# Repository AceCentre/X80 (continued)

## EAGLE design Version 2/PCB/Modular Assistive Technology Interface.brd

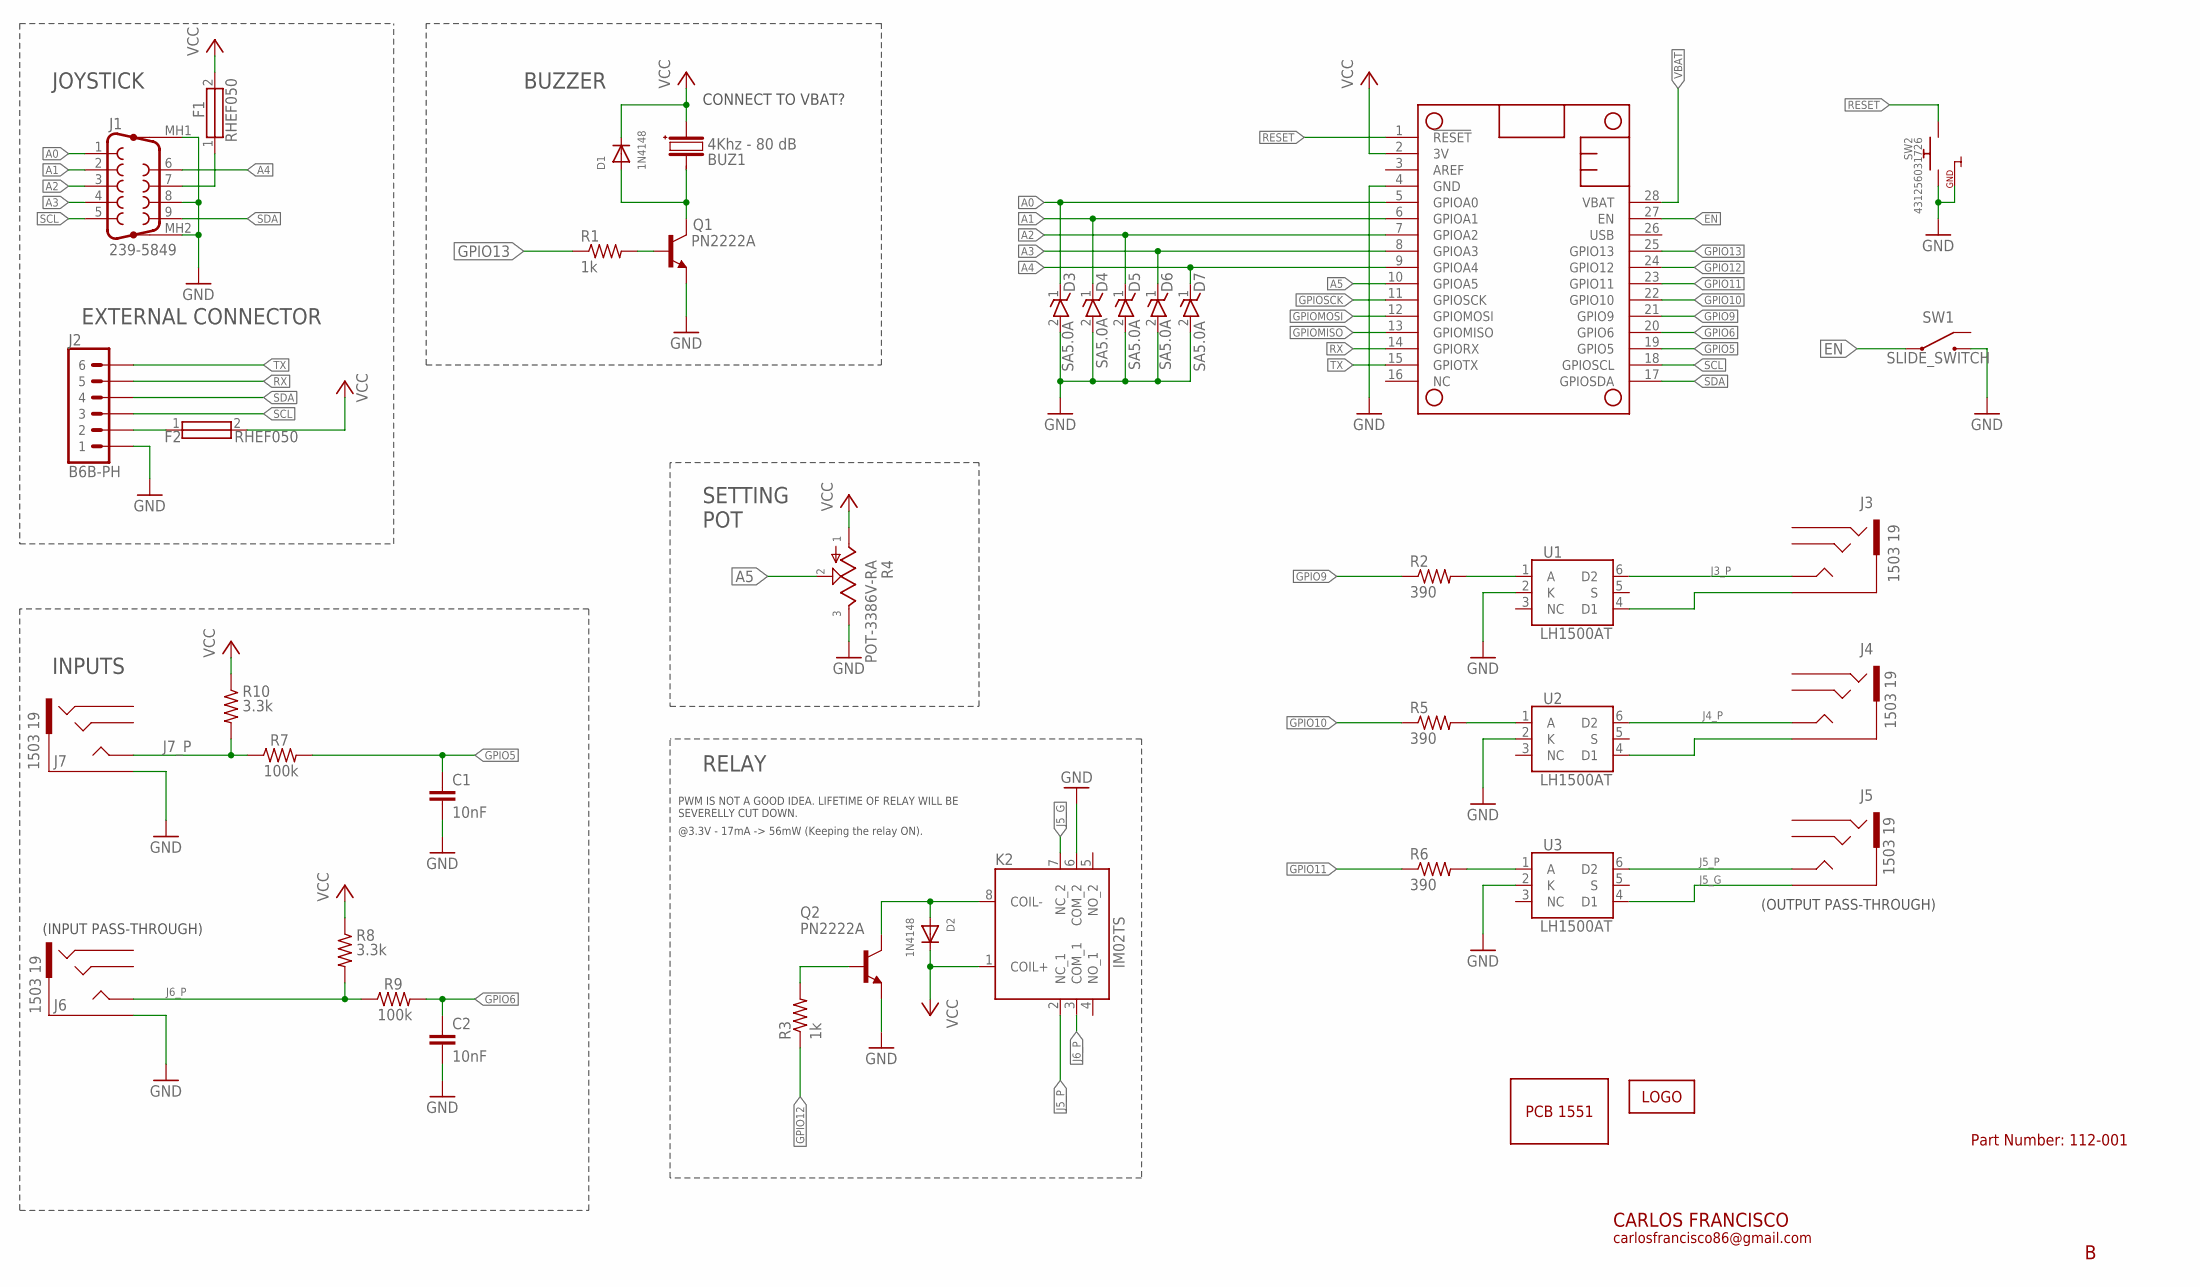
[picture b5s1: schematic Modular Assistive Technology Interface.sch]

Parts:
BUZ1: 4Khz - 80 dB; -511-7620
C1, C2: 10nF; C025-024X044
D1, D2: 1N4148; DO-1N4148
D3, D4, D5, D6, D7: SA5.0A; DIOAD1910W86L670D310
F1, F2: RHEF050
J1: 239-5849; DB9_PLUG_SLOT
J2: B6B-PH; SHDR6W50P0X200_1X6_990X450X600
J3, J4, J5, J6, J7: 1503 19; 1503-19
K2: IM02TS; IM03TS114620378
MS1: FEATHERWING_NODIM; FEATHERWING_DIM
Q1, Q2: PN2222A; TO92-EBC-OVAL
R1, R3: 1k; 0207/10
R2, R5, R6: 390; 0207/10
R4: POT-3386V-RA; 3386V1103LF
R7, R9: 100k; 0207/10
R8, R10: 3.3k; 0207/10
SW1: SLIDE_SWITCH; OS102011MA1QN1
SW2: 431256031726; SERIES95C_RA
U1, U2, U3: LH1500AT; DIP762W47P254L880H410Q6N
U$2: LOGO-10MM; LOGO_10MM
U$3: PCB_1551-1551; PCB

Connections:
A0: D3.1 (K), J1.1, MS1.5 (GPIOA0)
A1: D4.1 (K), J1.2, MS1.6 (GPIOA1)
A2: D5.1 (K), J1.3, MS1.7 (GPIOA2)
A3: D6.1 (K), J1.4, MS1.8 (GPIOA3)
A4: D7.1 (K), J1.6, MS1.9 (GPIOA4)
A5: MS1.10 (GPIOA5), R4.2
BUZ_CTRL_R: Q1.B, R1.2
EN: MS1.27 (EN), SW1.2
GND: C1.2, C2.2, D3.2 (A), D4.2 (A), D5.2 (A), D6.2 (A), D7.2 (A), J1.8, J1.MH1 (G1), J1.MH2 (G2), J2.1, J6.1, J7.1, K2.6 (COM_2), MS1.4 (GND), Q1.E, Q2.E, R4.3, SW1.1, SW2.F1 (GND), SW2.F2 (GND), SW2.T2 (SW2), U1.2 (K), U2.2 (K), U3.2 (K)
GPIO5: C1.1, MS1.19 (GPIO5), R7.2
GPIO6: C2.1, MS1.20 (GPIO6), R9.2
GPIO9: MS1.21 (GPIO9), R2.1
GPIO10: MS1.22 (GPIO10), R5.1
GPIO11: MS1.23 (GPIO11), R6.1
GPIO12: MS1.24 (GPIO12), R3.1
GPIO13: MS1.25 (GPIO13), R1.1
GPIOMISO: MS1.13 (GPIOMISO)
GPIOMOSI: MS1.12 (GPIOMOSI)
GPIOSCK: MS1.11 (GPIOSCK)
J3_P: J3.4, J3.5 (4), U1.6 (D2)
J4_P: J4.4, J4.5 (4), U2.6 (D2)
J5_G: J5.1, K2.7 (NC_2), U3.4 (D1)
J5_P: J5.4, J5.5 (4), K2.2 (NC_1), U3.6 (D2)
J6_P: J6.4, J6.5 (4), K2.3 (COM_1), R8.2, R9.1
J7_P: J7.4, J7.5 (4), R7.1, R10.2
unnamed: BUZ1.-, D1.A, Q1.C
unnamed: J3.1, U1.4 (D1)
unnamed: J4.1, U2.4 (D1)
unnamed: R2.2, U1.1 (A)
unnamed: R5.2, U2.1 (A)
unnamed: R6.2, U3.1 (A)
unnamed: F2.1, J2.2
unnamed: D2.A, K2.8 (COIL-), Q2.C
unnamed: Q2.B, R3.2
unnamed: F1.1, J1.7
RESET: MS1.1 (!RESET), SW2.T1 (SW1)
RX: J2.5, MS1.14 (GPIORX)
SCL: J1.5, J2.3, MS1.18 (GPIOSCL)
SDA: J1.9, J2.4, MS1.17 (GPIOSDA)
TX: J2.6, MS1.15 (GPIOTX)
VBAT: MS1.28 (VBAT)
VCC: BUZ1.+, D1.C, D2.C, F1.2, F2.2, K2.1 (COIL+), MS1.2 (3V), R4.1, R8.1, R10.1

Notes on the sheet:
CONNECT TO VBAT?
CARLOS FRANCISCO
carlosfrancisco86@gmail.com
BUZZER
JOYSTICK
EXTERNAL CONNECTOR
SETTING POT
(INPUT PASS-THROUGH)
INPUTS
(OUTPUT PASS-THROUGH)
RELAY
PWM IS NOT A GOOD IDEA. LIFETIME OF RELAY WILL BE SEVERELLY CUT DOWN.
Part Number: 112-001
@3.3V - 17mA -> 56mW (Keeping the relay ON).

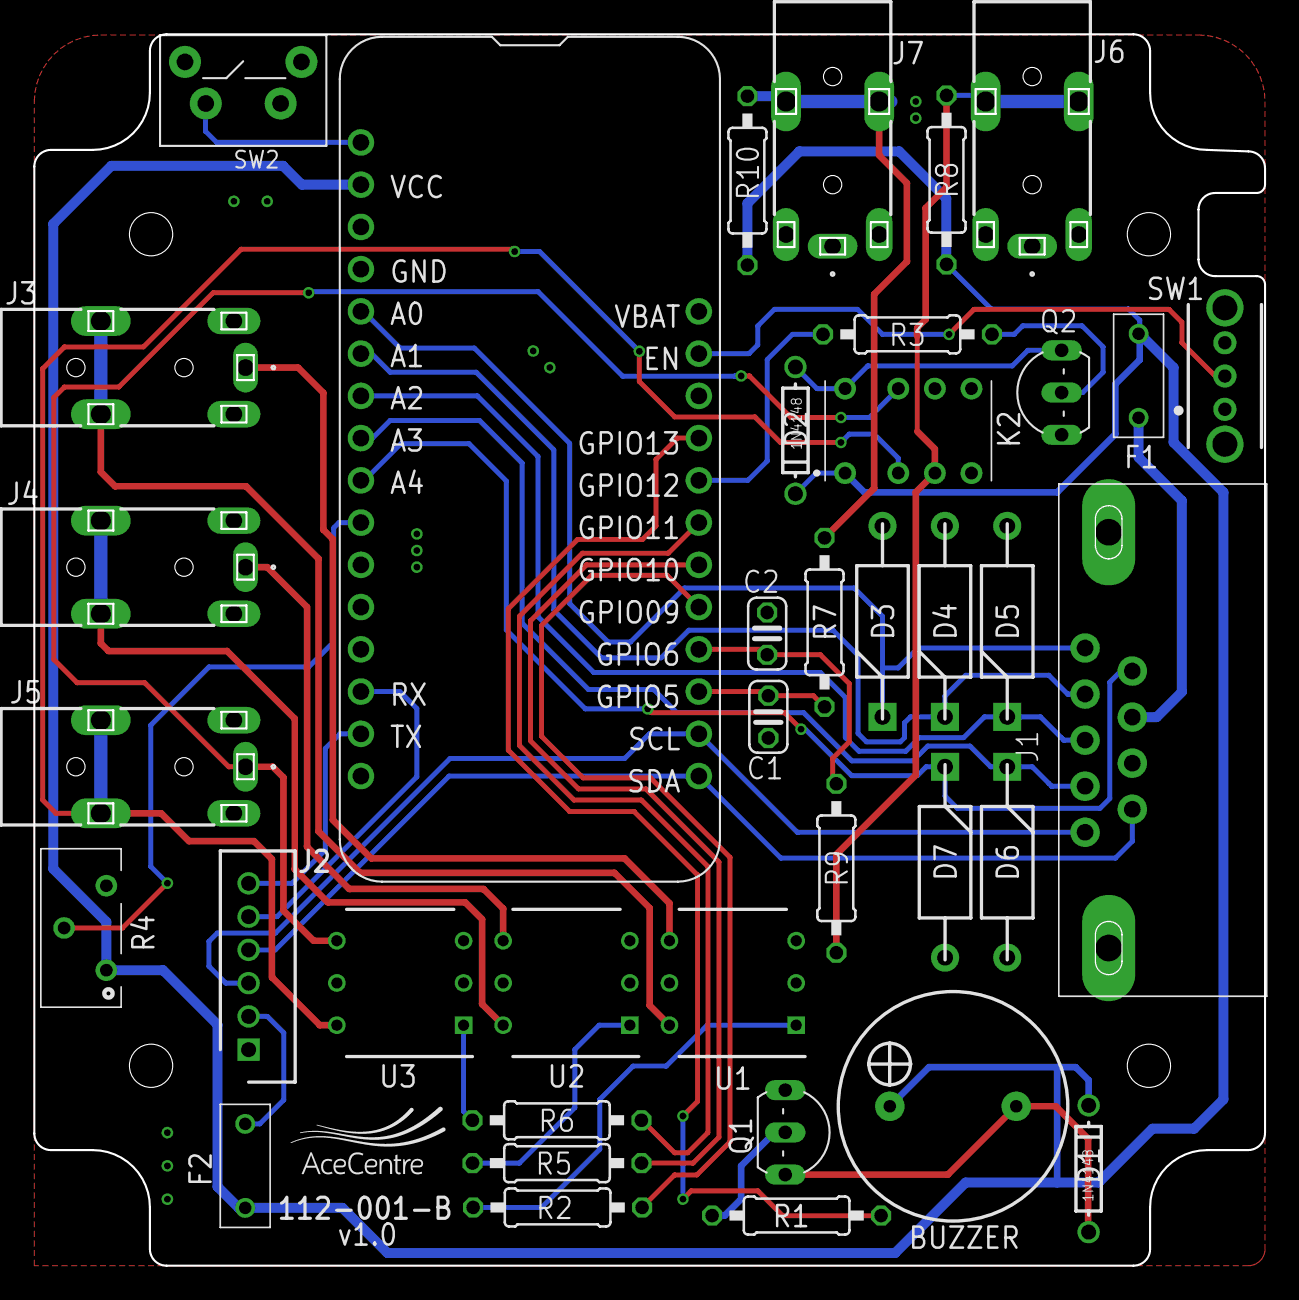
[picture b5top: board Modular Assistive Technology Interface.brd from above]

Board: 2 copper layers, 74.0 x 74.0 mm, 40 parts (0 on the bottom side), 38 nets.

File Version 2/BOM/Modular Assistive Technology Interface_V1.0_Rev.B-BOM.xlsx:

Item # | Ref Des | Qty | Description | Manufacturer | Manufacturer part-name | Value | Package | RS-ONLINE_NUM
1 | BUZ1 | 1 | 80dB, Through Hole Continuous Internal Piezo Buzzer | RS-PRO | 511-7620 | 4Khz, 80dB | THT | 511-7620
2 | C1, C2 | 2 | 10nF Multilayer Ceramic Capacitor MLCC 50V dc ±10% | KEMET | C315C103K5R5TA | 10nF | THT | 538-1196
3 | D1, D2 | 2 | Switching Diode, 400mA 100V, 2-Pin DO-35 1N4148TR | On Semiconductor | 1N4148TR | 1N4148 | THT | 671-5477
4 | D3, D4, D5, D6, D7 | 5 | SA5.0A, Uni-Directional TVS Diode, 500W, 2-Pin DO-204AC | Littelfuse | SA5.0A | 9.2V | THT | 764-5521
5 | F1, F2 | 2 | 0.5A Radial Leaded PCB Mount Resettable Fuse, 30 V | Littelfuse | RHEF050 | 0.5A | THT | 506-971
6 | J1 | 1 | D-sub Connector - 2.77mm Pitch | RS-PRO | 239-5849 | 239-5849 | THT | 239-5849
7 | J2 | 1 | JST, PH, B6B, 6 Way, 1 Row, Straight PCB Header | JST | B6B-PH-K-S(LF)(SN) | B6B-PH | THT | 820-1447
8 | J3, J4, J5, J6, J7 | 5 | 3.5 mm PCB Mount Stereo Jack Socket, 4Pole 1A | Lumberg | 1503 19 | Jack | THT | 124-8885
9 | K2 | 1 | DPDT telecom PCB relay, 2A 5Vdc coil, EA | TE Connectivity | IM02TS | DPDT Relay | THT | 422-7013
10 | Q1, Q2 | 2 | NPN General-Purpose Amplifier | On Semiconductor | PN2222ABU | PN2222A | THT | 739-0555
11 | R1, R3 | 2 | RS PRO 1kΩ Carbon Film Resistor 0.25W ±5% | RS-PRO | 707-7666 | 1k | THT | 707-7666
12 | R2, R5, R6 | 3 | RS PRO 390Ω Carbon Film Resistor 0.25W ±5% | RS-PRO | 707-7634 | 390R | THT | 707-7634
13 | R4 | 1 | 10kΩ, ±10%, 0.5W Linear potentiometer | Bourns | 3386V-1-103LF | 10k | THT | 691-7658
14 | R7, R9 | 2 | RS PRO 100kΩ Carbon Film Resistor 0.25W ±5% | RS-PRO | 707-7824 | 100k | THT | 707-7824
15 | R8, R10 | 2 | RS PRO 3.3kΩ Carbon Film Resistor 0.25W ±5% | RS-PRO | 707-7701 | 3,3k | THT | 707-7701
16 | SW1 | 1 | Through Hole Slide Switch Single Pole Double Throw (SPDT) | C&K Components | OS102011MA1QN1 | SPDT | THT | 787-4855
17 | SW2 | 1 | Tactile Switch, Single Pole Single Throw (SPST) 50 mA @ 12 V | Wurth Elektronik | 431256031726 | 431256031726 | THT | 785-6386
18 | U1, U2, U3 | 3 | 1 Form A Solid-State Relay (NO) | Vishay | LH1500AT | LH1500AT | THT | 180-8794
19 | Socket Headers (Feather) x16 | 1 | SSW 2.54mm Pitch 16 Way 1 Row Straight PCB Socket | Samtec | SSW-116-01-G-S | 16-Way | THT | 765-5792
20 | Socket Headers (Feather) x12 | 1 | SSW 2.54mm Pitch 12 Way 1 Row Straight PCB Socket | Samtec | SSW-112-01-G-S | 12-Way | THT | 765-5751

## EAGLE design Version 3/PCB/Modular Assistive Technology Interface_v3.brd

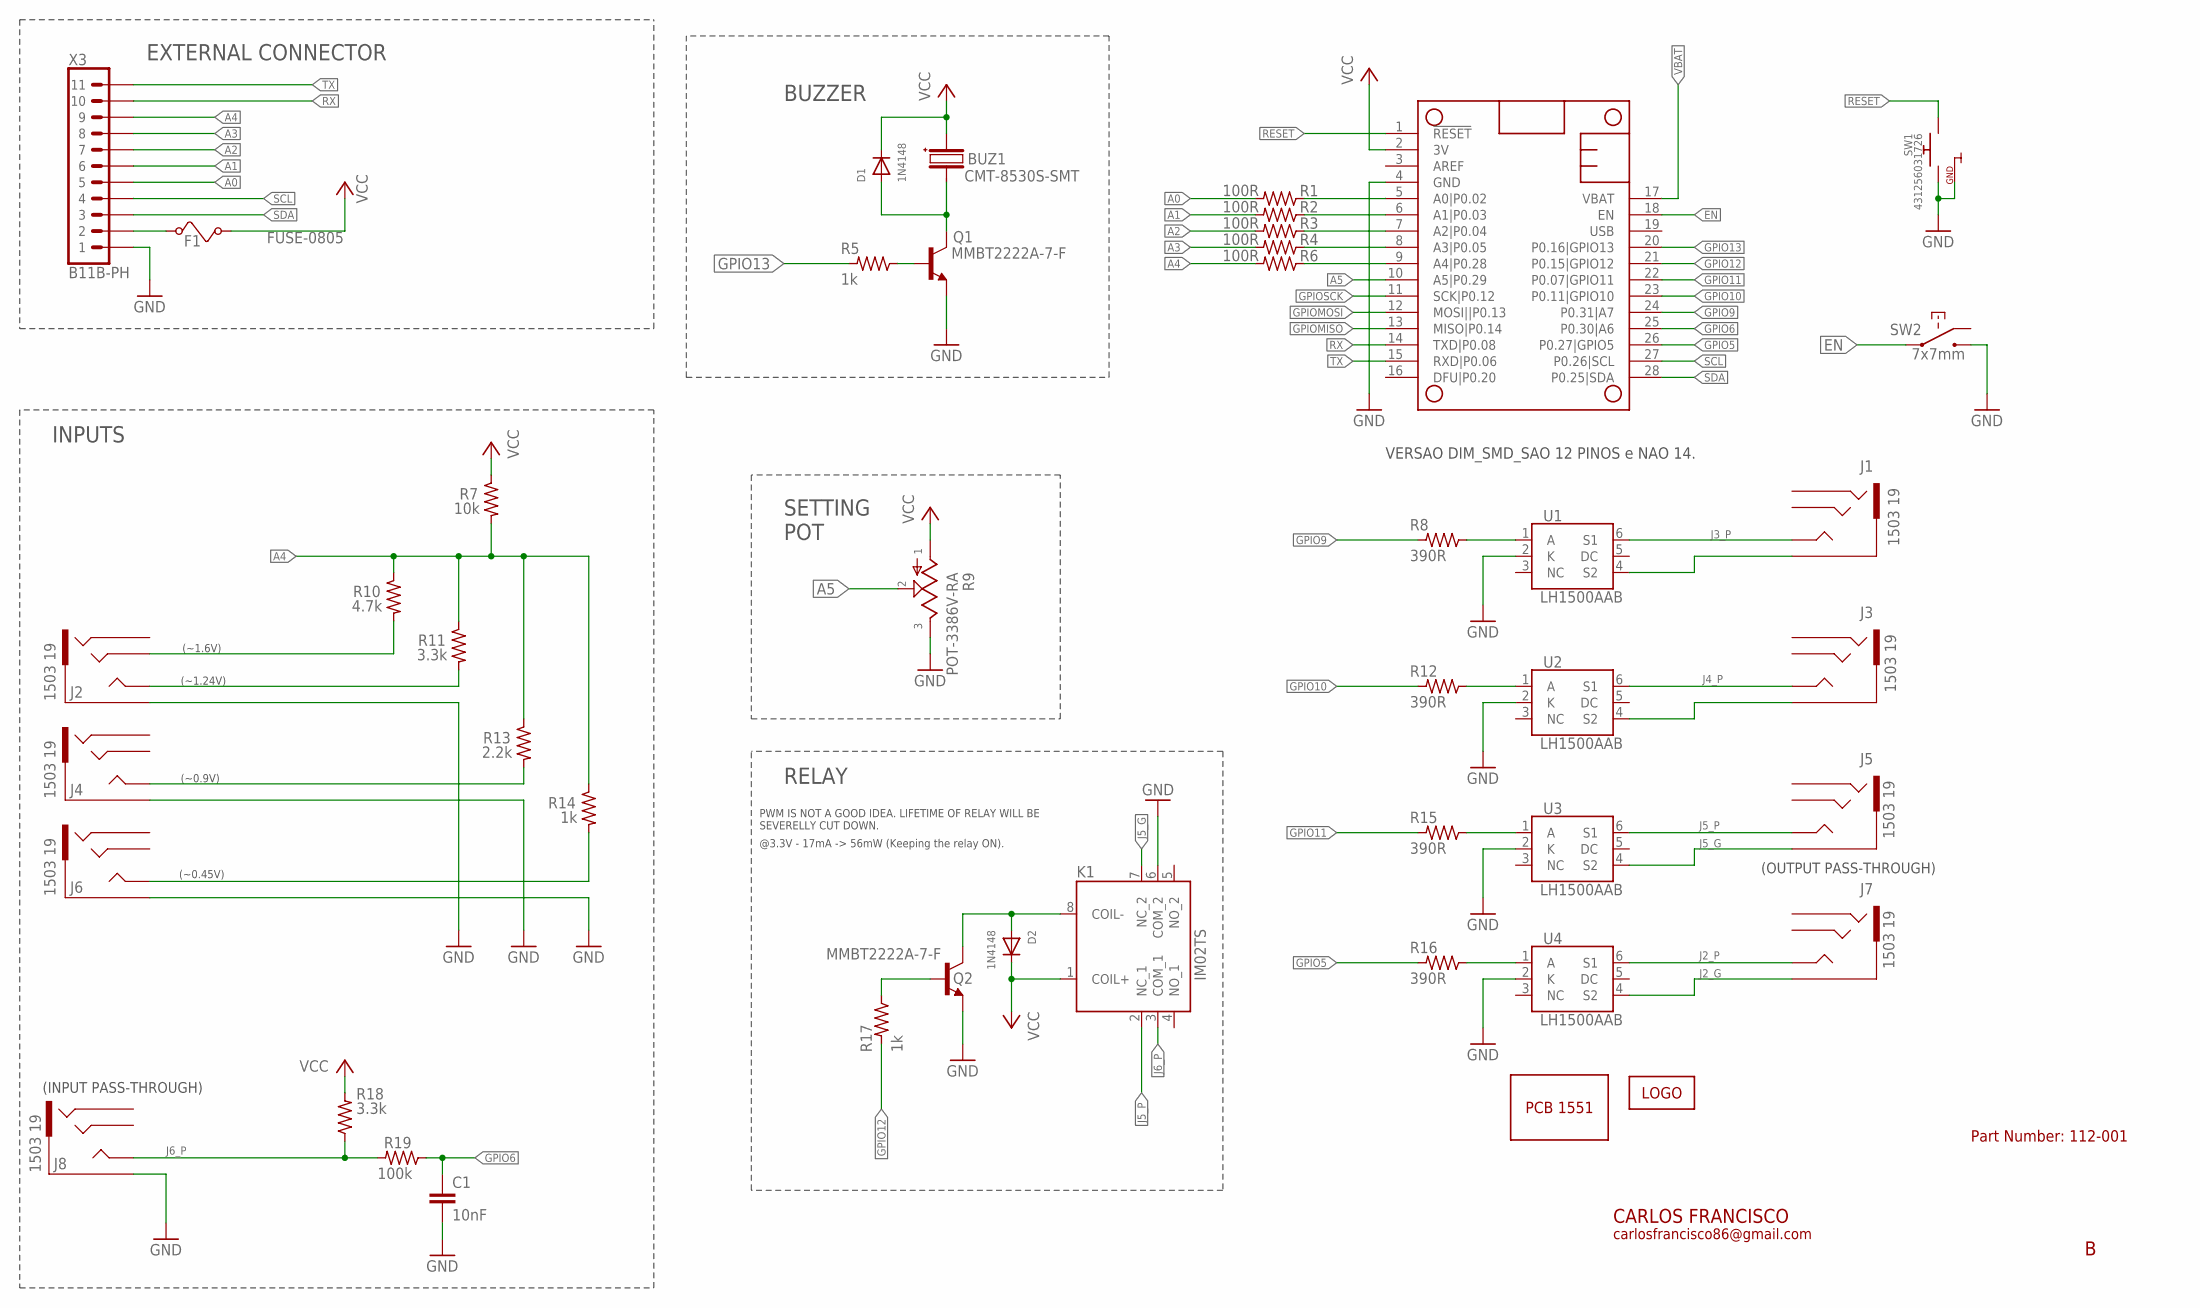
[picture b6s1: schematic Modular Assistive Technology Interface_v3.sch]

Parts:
BUZ1: CMT-8530S-SMT; CMT8530SSMTTR
C1: 10nF; CAPC1608X85
D1, D2: 1N4148; SOD-123
F1: FUSE-0805; 0ZCK0050AF2E
J1, J2, J3, J4, J5, J6, J7, J8: 1503 19; 1503-19
K1: IM02TS; IM03TS114620378
LOGO1: LOGO-10MM; LOGO_10MM
MS1: FEATHERWING-NODIIM_SMD; FEATHERWING_DIM_SMD
PCB1: PCB_1551-V4; PCB_V4
Q1, Q2: MMBT2222A-7-F; SOT-23
R1, R2, R3, R4, R6: 100R; R0603
R5, R14, R17: 1k; R0603
R7: 10k; R0603
R8, R12, R15, R16: 390R; R0603
R9: POT-3386V-RA; 3386V1103LF
R10: 4.7k; R0603
R11, R18: 3.3k; R0603
R13: 2.2k; R0603
R19: 100k; R0603
SW1: 431256031726; SERIES95C_RA
SW2: 7x7mm; 7X7MM_LATCHING
U1, U2, U3, U4: LH1500AAB; SOT254P983X406-6N
X3: B11B-PH; SHDR6W50P0X200_1X11_990X450X600

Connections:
A0: R1.1, X3.5
A0_R: MS1.5 (A0|P0.02), R1.2
A1: R2.1, X3.6
A1_R: MS1.6 (A1|P0.03), R2.2
A2: R3.1, X3.7
A2_R: MS1.7 (A2|P0.04), R3.2
A3: R4.1, X3.8
A3_R: MS1.8 (A3|P0.05), R4.2
A4: R6.1, R7.1, R10.2, R11.2, R13.2, R14.2, X3.9
A4_R: MS1.9 (A4|P0.28), R6.2
A5: MS1.10 (A5|P0.29), R9.2
BUZ_CTRL_R: Q1.B, R5.2
EN: MS1.18 (EN), SW2.P$2 (C), SW2.P$5 (C)
GND: C1.2, J2.1, J4.1, J6.1, J8.1, K1.6 (COM_2), MS1.4 (GND), Q1.E, Q2.E, R9.3, SW1.F1 (GND), SW1.F2 (GND), SW1.T2 (SW2), SW2.P$1 (NO), SW2.P$4 (NO), U1.2 (K), U2.2 (K), U3.2 (K), U4.2 (K), X3.1
GPIO5: MS1.26 (P0.27|GPIO5), R16.1
GPIO6: C1.1, MS1.25 (P0.30|A6), R19.2
GPIO9: MS1.24 (P0.31|A7), R8.1
GPIO10: MS1.23 (P0.11|GPIO10), R12.1
GPIO11: MS1.22 (P0.07|GPIO11), R15.1
GPIO12: MS1.21 (P0.15|GPIO12), R17.1
GPIO13: MS1.20 (P0.16|GPIO13), R5.1
GPIOMISO: MS1.13 (MISO|P0.14)
GPIOMOSI: MS1.12 (MOSI||P0.13)
GPIOSCK: MS1.11 (SCK|P0.12)
IN1: J6.4, J6.5 (4), R14.1
IN2: J4.4, J4.5 (4), R13.1
IN3: J2.4, J2.5 (4), R11.1
IN4: J2.3, R10.1
J2_G: J7.1, U4.4 (S2)
J2_P: J7.4, J7.5 (4), U4.6 (S1)
J3_P: J1.4, J1.5 (4), U1.6 (S1)
J4_P: J3.4, J3.5 (4), U2.6 (S1)
J5_G: J5.1, K1.7 (NC_2), U3.4 (S2)
J5_P: J5.4, J5.5 (4), K1.2 (NC_1), U3.6 (S1)
J6_P: J8.4, J8.5 (4), K1.3 (COM_1), R18.2, R19.1
unnamed: BUZ1.3 (-), D1.A, Q1.C
unnamed: J1.1, U1.4 (S2)
unnamed: J3.1, U2.4 (S2)
unnamed: R8.2, U1.1 (A)
unnamed: R12.2, U2.1 (A)
unnamed: R16.2, U4.1 (A)
unnamed: R15.2, U3.1 (A)
unnamed: F1.1, X3.2
unnamed: D2.A, K1.8 (COIL-), Q2.C
unnamed: Q2.B, R17.2
RESET: MS1.1 (!RESET), SW1.T1 (SW1)
RX: MS1.14 (TXD|P0.08), X3.10
SCL: MS1.27 (P0.26|SCL), X3.4
SDA: MS1.28 (P0.25|SDA), X3.3
TX: MS1.15 (RXD|P0.06), X3.11
VBAT: MS1.17 (VBAT)
VCC: BUZ1.2 (+), D1.C, D2.C, F1.2, K1.1 (COIL+), MS1.2 (3V), R7.2, R9.1, R18.1

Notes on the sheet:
CARLOS FRANCISCO
carlosfrancisco86@gmail.com
BUZZER
EXTERNAL CONNECTOR
SETTING POT
(INPUT PASS-THROUGH)
INPUTS
(OUTPUT PASS-THROUGH)
RELAY
PWM IS NOT A GOOD IDEA. LIFETIME OF RELAY WILL BE SEVERELLY CUT DOWN.
Part Number: 112-001
@3.3V - 17mA -> 56mW (Keeping the relay ON).
VERSAO DIM_SMD_SAO 12 PINOS e NAO 14.
(~1.6V)
(~1.24V)
(~0.9V)
(~0.45V)

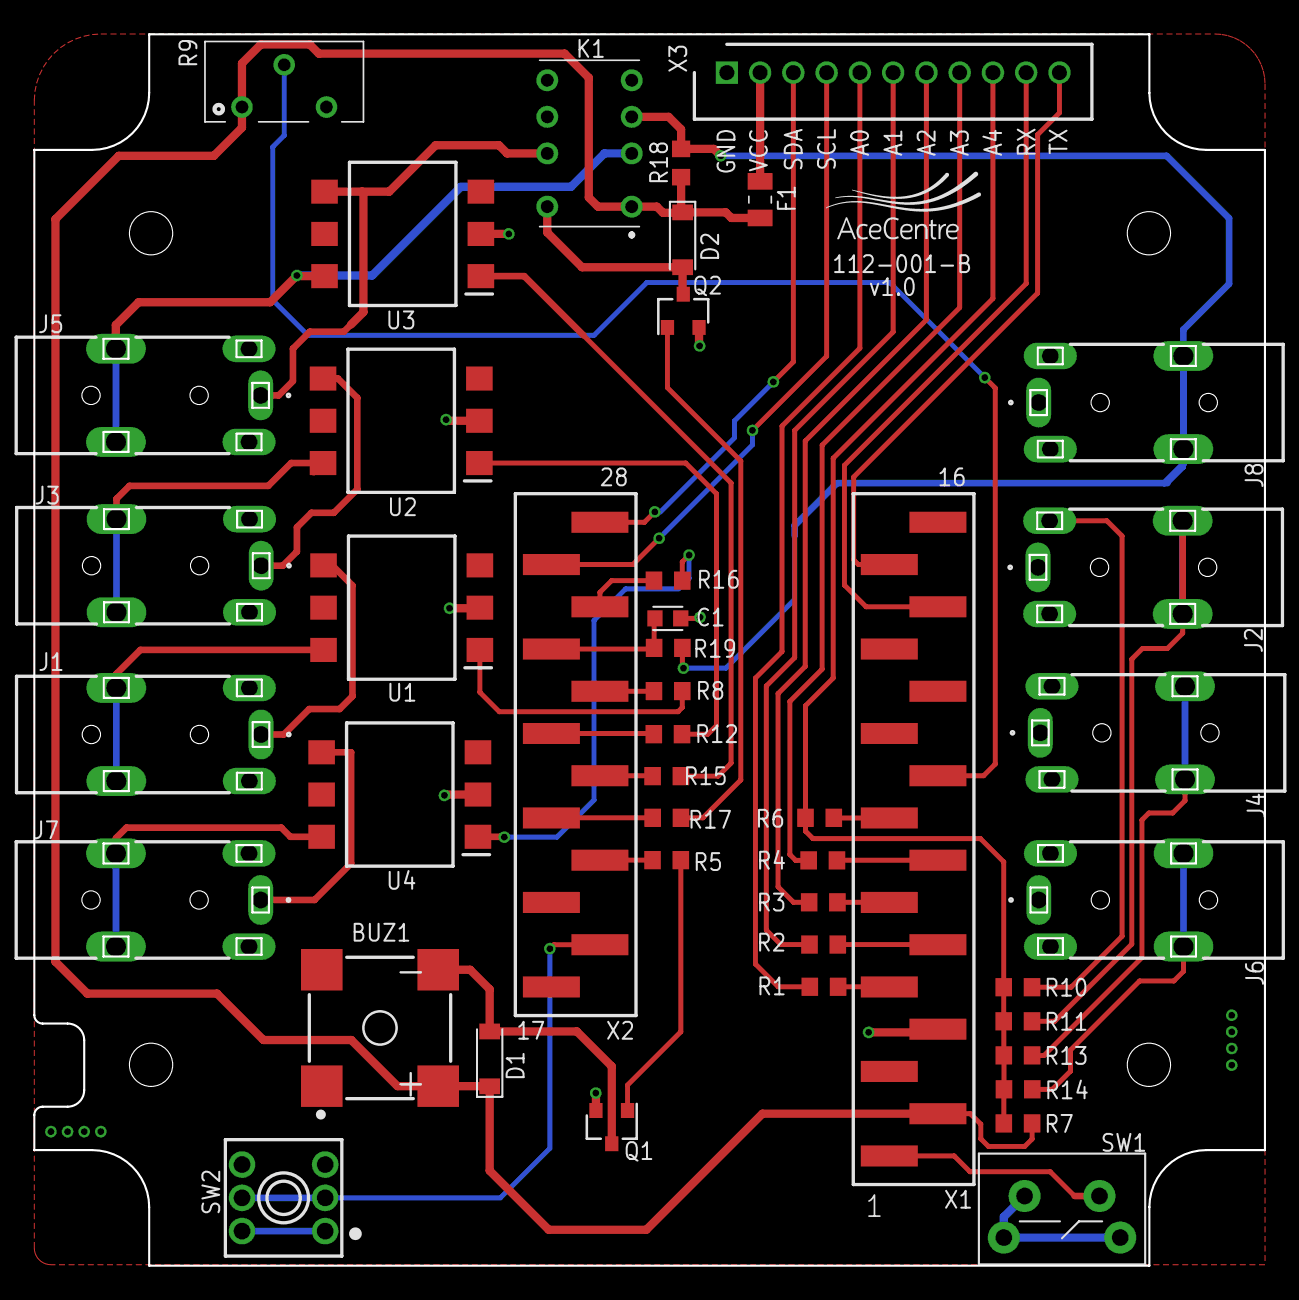
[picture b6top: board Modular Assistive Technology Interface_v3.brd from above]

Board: 2 copper layers, 74.0 x 74.0 mm, 45 parts (0 on the bottom side), 48 nets.

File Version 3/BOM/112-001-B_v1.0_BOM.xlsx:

Ref | Description | Value | Footprint | Manufacturer Name | Manufacturer/MPN | Quantity | Original
BUZ1 | AUDIO MAGNETIC XDCR 3-5V SMD | 87dB | SMD-4 | Cui Devices | CMT-8530S-SMT-TR | 1
C1 | CAP CER 10NF 50V X7R 0603 | 10nF | 0603 | Samsung | CL10B103KB8WPJC | 1
D1, D2 | DIODE GEN PURP 75V 150MA SOD123 | 1N4148 | SOD-123 | Vishay | 1N4148W-G3-08 | 2
F1 | PTC RESET FUSE 9V 500MA 0805 | 6V, 0.5A | 0805 | Bel Fuse | 0ZCK0050AF2E | 1
J1, J2, J3, J4, J5, J6, J7, J8 | Lumberg 3.5 mm PCB Mount Stereo Jack Socket, 4Pole 1A | 1503 19 | THT | Lumberg | 1503 19 | 8
K1 | DPDT telecom PCB relay, 2A 5Vdc coil, EA | IM02TS | THT | TE Connectivity | IM03TS 1-1462037-8 | 1
Q1, Q2 | TRANS NPN 40V 0.6A SMD SOT23-3 | MMBT2222A-7-F | SOT-23 | Diodes Incorporated | MMBT2222A-7-F | 2
R1, R2, R3, R4, R6 | RES SMD 100 OHM 1% 1/10W 0603 | 100R | 0603 | Yageo | RC0603FR-07100RL | 5
R10 | RES SMD 4.7K OHM 1% 1/10W 0603 | 4.7k | 0603 | Yageo | RC0603FR-074K7L | 1
R11, R18 | RES SMD 3.3K OHM 1% 1/10W 0603 | 3.3k | 0603 | Yageo | RC0603FR-073K3L | 2
R13 | RES SMD 2.2K OHM 1% 1/10W 0603 | 2.2k | 0603 | Yageo | RC0603FR-072K2L | 1
R19 | RES SMD 100K OHM 1% 1/10W 0603 | 100k | 0603 | Yageo | RC0603FR-07100KL | 1
R5, R14, R17 | RES 1K OHM 0.1% 1/10W 0603 | 1k | 0603 | Yageo | RC0603FR-071KL | 3
R7 | RES SMD 10K OHM 1% 1/10W 0603 | 10k | 0603 | Yageo | RC0603FR-0710KL | 1
R8, R12, R15, R16 | RES SMD 390 OHM 5% 1/10W 0603 | 390R | 0603 | Yageo | RC0603JR-07390RL | 4
R9 | 10kΩ, ±10%, 0.5W Linear potentiometer | 10k | THT | Bourns | 3386V-1-103LF | 1
SW1 | Tactile Switch, Single Pole Single Throw (SPST) 50 mA @ 12 V | 431256031726 | DNP | Wurth Elektronik |  | 1
SW2 | SPDT Push Button Switch Self Latching Locking 3 Pin DIP PCB MOUNT 7 x 7mm | 7x7mm | THT | XKB Enterprise | XKB7070-Z | 1
U1, U2, U3, U4 | SSR RELAY SPST-NO 150MA 0-350V | LH1500AAB | SMD-6 | Vishay Semiconductor Opto Division | 54-00133 | 4
X1 | CONN HEADER SMD 16POS 2.54MM | TSM-116-01-T-SV-P | THT | Samtec | TSM-116-01-T-SV-P | 1
X2 | CONN HEADER SMD 12POS 2.54MM | TSM-112-01-T-SV-P | THT | Samtec | TSM-112-01-T-SV-P | 1
X3 | CONN HEADER VERT 11POS 2MM | B11B-PH |  | JST | B11B-PH-K(LF)(SN) | 1

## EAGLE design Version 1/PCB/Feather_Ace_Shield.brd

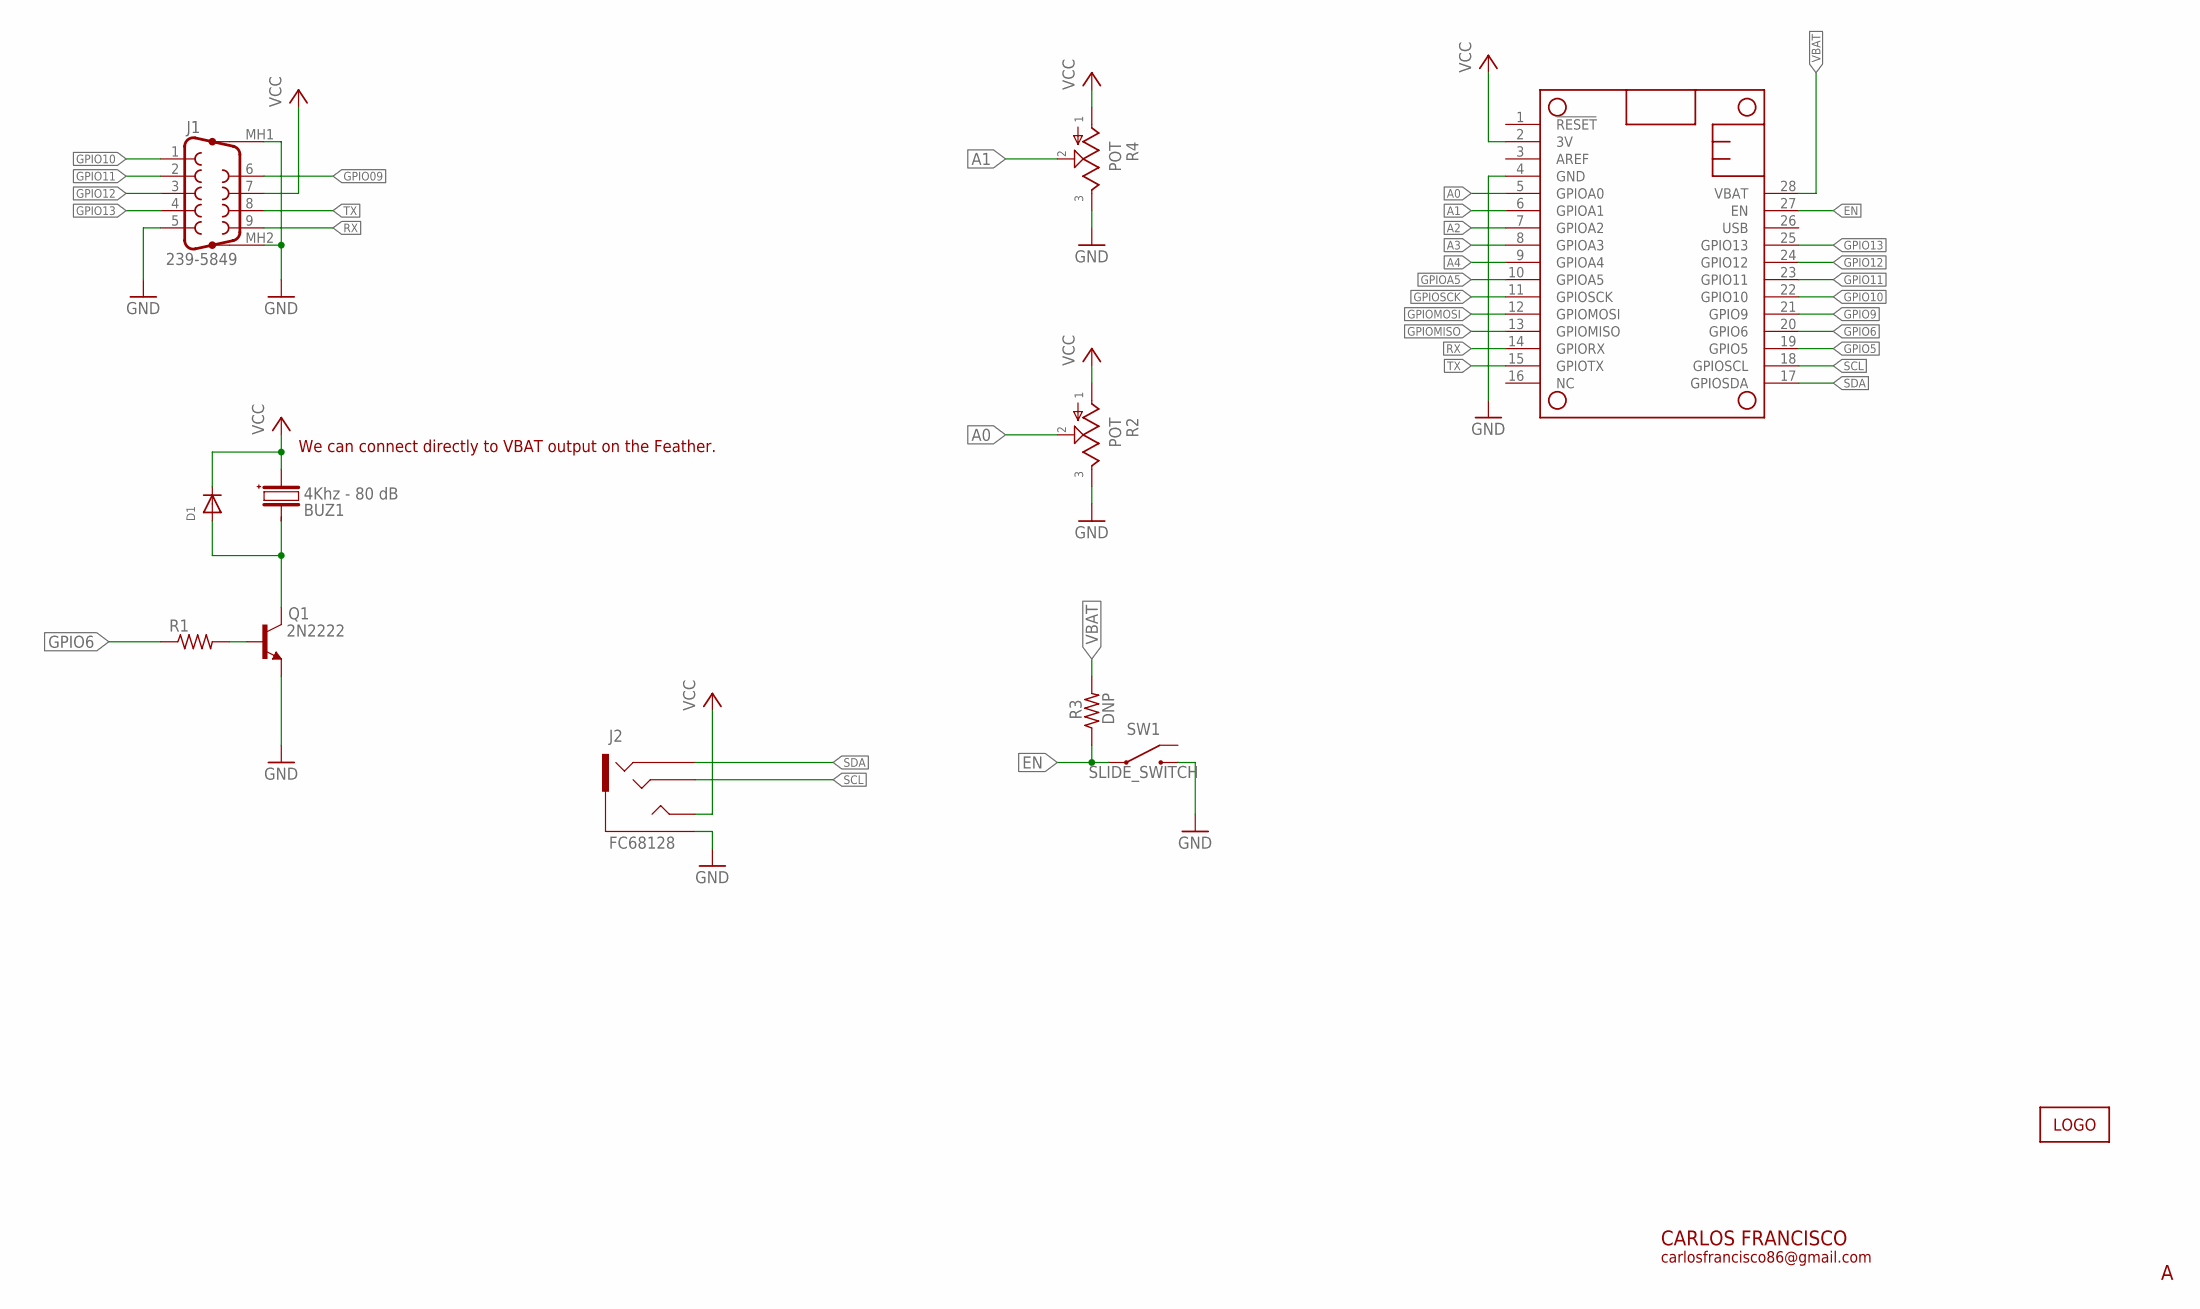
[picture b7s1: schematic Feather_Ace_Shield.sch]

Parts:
BUZ1: 4Khz - 80 dB; -511-7620
D1: DIODEDO-1N4148; DO-1N4148
J1: 239-5849; DB9_PLUG
J2: FC68128
MS1: FEATHERWING_NODIM; FEATHERWING_DIM
Q1: 2N2222; TO92-EBC-OVAL
R1: R-US_0207/10; 0207/10
R2, R4: POT; 3386P_1
R3: DNP; 0207/10
SW1: SLIDE_SWITCH; OS102011MA1QN1
U$2: LOGO-10MM; LOGO_10MM

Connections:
A0: MS1.5 (GPIOA0), R2.2
A1: MS1.6 (GPIOA1), R4.2
A2: MS1.7 (GPIOA2)
A3: MS1.8 (GPIOA3)
A4: MS1.9 (GPIOA4)
BUZ_CTRL_R: Q1.B, R1.2
EN: MS1.27 (EN), R3.1, SW1.2
GND: J1.5, J1.MH1 (G1), J1.MH2 (G2), J2.1S_L (1S_SLEEVE), J2.1S_R (1S_SLEEVE), MS1.4 (GND), Q1.E, R2.3, R4.3, SW1.1
GPIO5: MS1.19 (GPIO5)
GPIO6: MS1.20 (GPIO6), R1.1
GPIO9: MS1.21 (GPIO9)
GPIO09: J1.6
GPIO10: J1.1, MS1.22 (GPIO10)
GPIO11: J1.2, MS1.23 (GPIO11)
GPIO12: J1.3, MS1.24 (GPIO12)
GPIO13: J1.4, MS1.25 (GPIO13)
GPIOA5: MS1.10 (GPIOA5)
GPIOMISO: MS1.13 (GPIOMISO)
GPIOMOSI: MS1.12 (GPIOMOSI)
GPIOSCK: MS1.11 (GPIOSCK)
unnamed: BUZ1.-, D1.A, Q1.C
RX: J1.9, MS1.14 (GPIORX)
SCL: J2.2R (2R_1RING), MS1.18 (GPIOSCL)
SDA: J2.6_L (6SR_2RING), J2.6_R (6SR_2RING), MS1.17 (GPIOSDA)
TX: J1.8, MS1.15 (GPIOTX)
VBAT: MS1.28 (VBAT), R3.2
VCC: BUZ1.+, D1.C, J1.7, J2.3T (3T_TIP), MS1.2 (3V), R2.1, R4.1

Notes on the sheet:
We can connect directly to VBAT output on the Feather.
CARLOS FRANCISCO
carlosfrancisco86@gmail.com

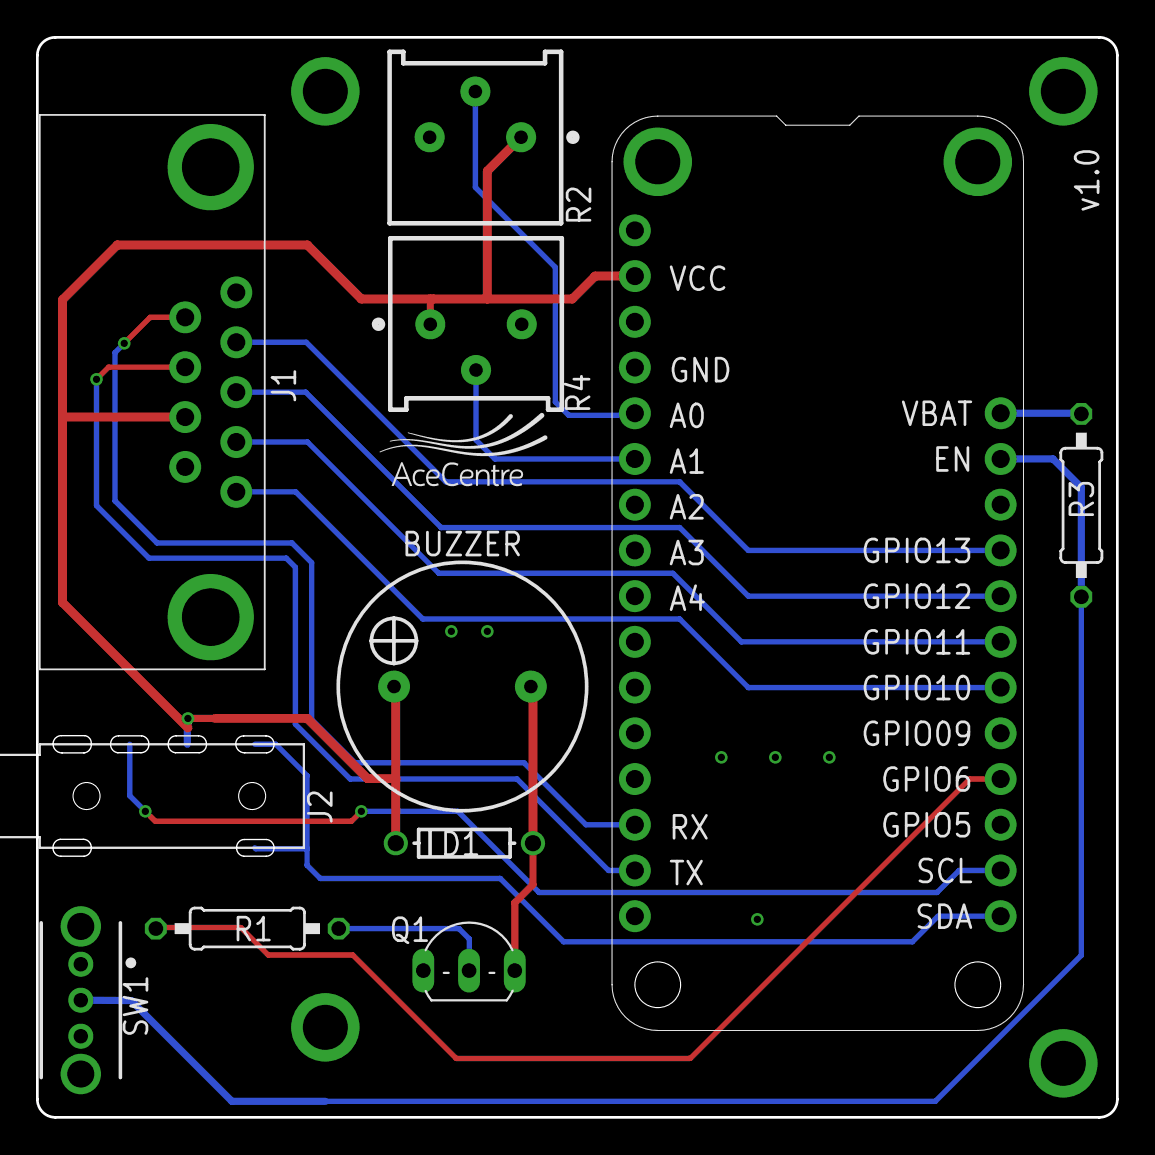
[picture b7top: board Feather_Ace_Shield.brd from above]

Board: 2 copper layers, 60.0 x 60.0 mm, 12 parts (0 on the bottom side), 17 nets.

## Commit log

2020-10-25 Multi starter file
2020-10-25 Create LICENSE
2020-10-26 Added simpler sketch testing switch output
2021-01-18 Create iOS-test.py
    Opens Photos.
2021-03-10 Folder structure updated for current versions
2021-08-08 Included Version 4
2021-08-08 Added PCB schematic pdf
2021-08-08 Corrected model number
2022-01-24 Changes made to hardware enclosures and folder structure
    Removed references to previous versions. Changed file structure to make easier to follow. Added example code.
2022-01-24 Lens and Mounting plate moved to parts folder
2022-02-09 adding other code & renaming folders
2022-02-09 adding circuitPy demo
2022-02-10 Enclosure updated
2022-02-10 Added switch switcher and blink
2022-06-14 Add v1 of circuit python
2022-06-14 Fix readme
2022-06-14 Add another longer term
2022-06-17 Python switcher now outputs
2022-06-17 Final version of switch switcher
2022-07-14 Ignore mac files
2022-07-14 Upload new switcher
2022-07-15 Add bluetooth switcher
2022-08-17 Add five switch remote
2022-08-22 Add a keyboard commad to do CTRL + TAB
2023-01-25 Adding Wireless Switch demo.
    NB: This won't work on an X80 right now. This works on any nrf52840 chipset and note to add LED and Switches for the right pins.
2023-01-25 adding in to-do
2023-01-25 fixing done items
2023-01-25 add a bit more info
2023-01-26 sleep functionality added
    If there is no switch presses for defined amount of time then the board goes into deep sleep.
    This amount of time can be adjusted with "sleep_timeout" variable at line 8.
    Default value is 5 seconds.
    To wake up boards it's needed to press the switch .
    First press will be for board wake up and after built in led will turn on board will be ready to transmit data.
    It takes about 1 second.
2023-01-26 adding words
2023-01-28 adding in start of demo python code
2023-01-28 Including battery details
2023-01-29 adding another issue ref
2023-02-02 adding test code
2023-02-06 deals with dropped packets
2023-02-09 deals with holding down the key
2023-02-13 ading new python code
2023-02-13 removing old test code
2023-02-13 fixing to-dos
2023-02-13 adding boards
2023-02-14 adding redirect warning
2023-02-23 BOM and schematic
2023-02-23 adding raw gerbers files
2023-03-20 adding some images
2024-03-25 adding presstester
2024-03-25 ahh pulser
